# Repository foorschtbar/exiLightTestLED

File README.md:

# exiLightTestLED

Add-on for [exiLight](https://github.com/foorschtbar/exiLight) to drive the test LED on the case.

## Driver

https://github.com/digistump/DigistumpArduino/releases

## Credits

3D Model _Digispark (Micro USB Version)_ from [Jan Cernik](https://grabcad.com/library/digispark-attiny85-micro-usb-version-1).

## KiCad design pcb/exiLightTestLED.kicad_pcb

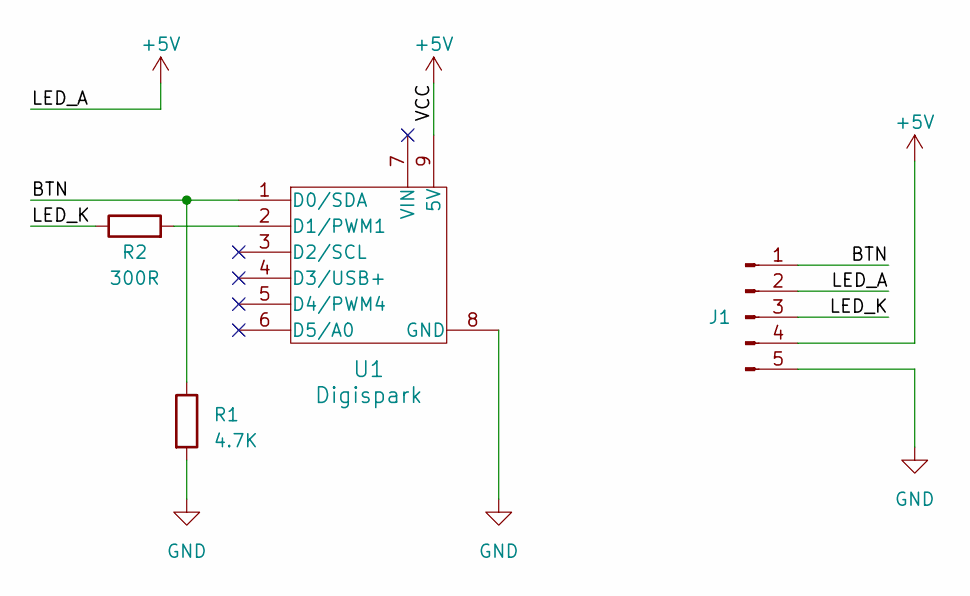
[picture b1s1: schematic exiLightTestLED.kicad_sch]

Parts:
J1: Conn_01x05_Pin; JST_PH_S5B-PH-K_1x05_P2.00mm_Horizontal
R1: 4.7K; R_0805_2012Metric_Pad1.20x1.40mm_HandSolder
R2: 300R; R_0805_2012Metric_Pad1.20x1.40mm_HandSolder
U1: Digispark; Digispark MicroUSB

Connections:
+5V: J1.2, J1.4, U1.9 (5V)
/BTN: J1.1, R1.1, U1.1 (D0/SDA)
/LED_K: J1.3, R2.1
GND: J1.5, R1.2, U1.8 (GND)
unnamed: R2.2, U1.2 (D1/PWM1)

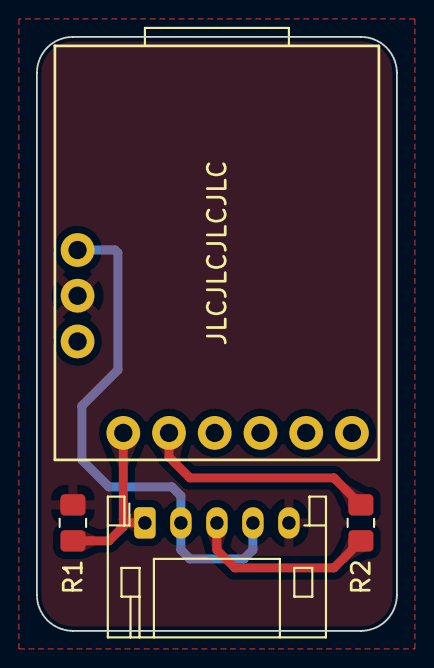
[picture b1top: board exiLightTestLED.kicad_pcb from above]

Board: 2 copper layers, 20.0 x 33.0 mm, 4 parts (0 on the bottom side), 5 nets.

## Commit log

2023-05-27 Inital commit
